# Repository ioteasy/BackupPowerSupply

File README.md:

# BackupPowerSupply
Module for backup power supply with 18650 - Li-ion battery

## Parameters
Input voltage: 5-24V

Output voltage Normal State: 4.4V

Output voltage Battery State: 4.3V

Max Current: 1A

## Used components
TPS54302 - Step-Down Converter (Input 4.5V-28V), Integrated MOSFETs for 3A continuous output current

LM2621 - Step-Up Converter (Input 1.2V-14V), Switch Current Limit 2.8A, Max switching frequenc 2MHz

MCP73831 - Single Cell Li-Ion Charge Management 

DW01 - Li-Ion Battery Protection

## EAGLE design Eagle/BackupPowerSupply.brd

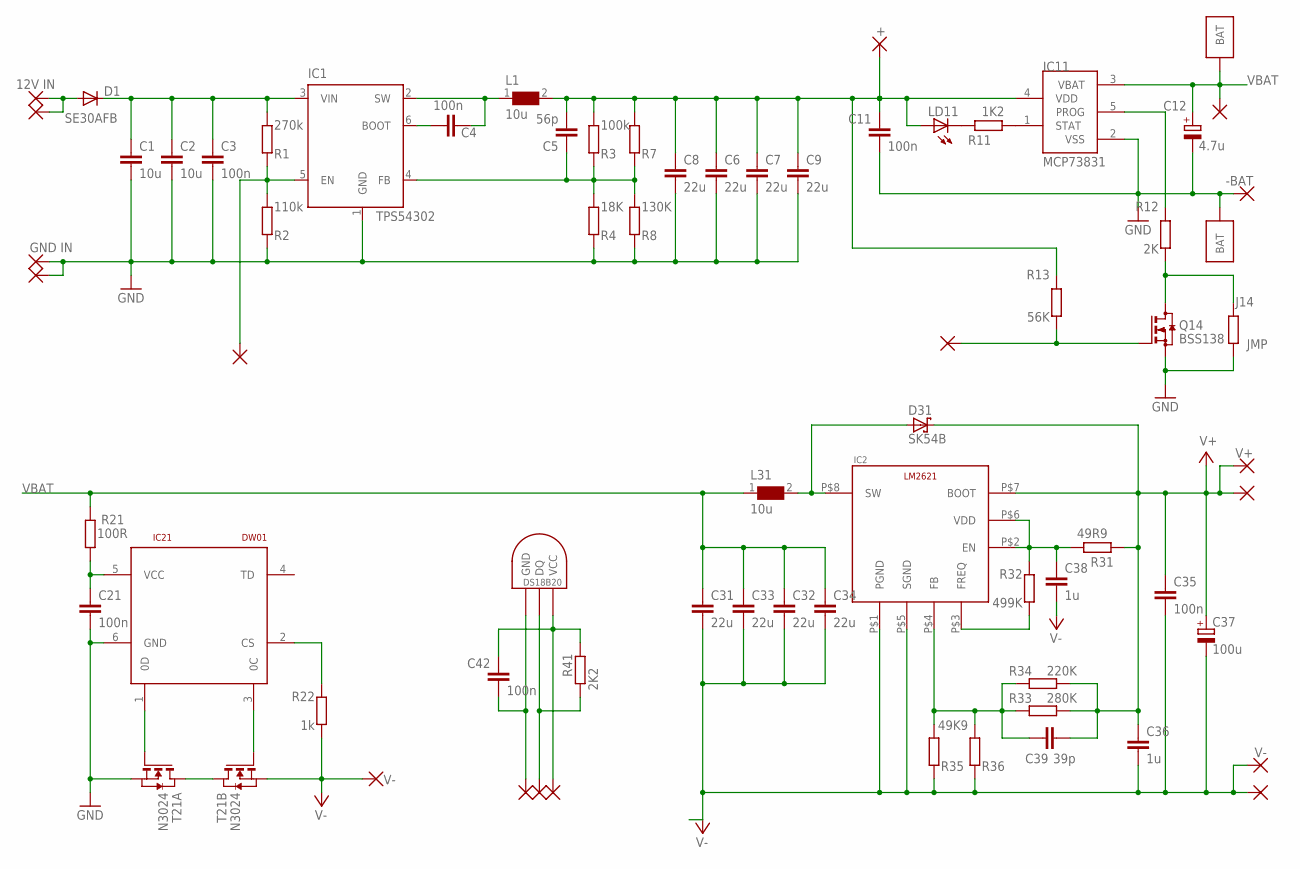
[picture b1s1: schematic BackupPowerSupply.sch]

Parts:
C1, C2: 10u; C1206
C3: 100n; C1206
C4, C11, C21, C35: 100n; C0805
C5: 56p; C0805
C6, C7, C8, C9, C31, C32, C33, C34: 22u; C0805
C12: 4.7u; SMC_A
C36, C38: 1u; C0805
C37: 100u; SMC_B
C39: 39p; C0805
C42: 100n; C0603
D1: SE30AFB; SOD-123_MINI-SMA
D31: SK54B; SMB
DS18B20: DS1820SOIC; DS18B20_SOIC
IC1: TPS54302; TSOT23-6_DDC
IC2: LM2621VSSOP8; VSSOP8
IC11: MCP73831; SOT23-5L
IC21: DW01; SOT23-6
J14: JMP; R0201
L1, L31: 10u; WE-LQS_8040
LD11: LEDCHIPLED_0805; CHIPLED_0805
PAD1: +BAT; PAD
PAD2: -BAT; PAD
PAD3: 12V IN; PAD
PAD4: GND IN; PAD
PAD5, PAD12: V+; PAD
PAD6, PAD9, PAD11, PAD19, PAD20, PAD21: V-; PAD
PAD7, PAD13: +; PAD
PAD8, PAD22: PAD
Q14: BSS138; SOT23
R1: 270k; M0805
R2: 110k; M0805
R3: 100k; M0805
R4: 18K; M0805
R7, R36: R-EU_M0805; M0805
R8: 130K; M0805
R11: 1K2; M0805
R12: 2K; M0805
R13: 56K; M0805
R21: 100R; M0805
R22: 1k; M0805
R31: 49R9; M0805
R32: 499K; M0805
R33: 280K; M0805
R34: 220K; M0805
R35: 49K9; M0805
R41: 2K2; R0603
T21: N3024; TSSOP-8
U$1, U$2: BAT_A
U$3: PAD

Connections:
C6: C5.2, IC1.4 (FB), R3.2, R4.1, R7.2, R8.1
FB2: C39.1, IC2.P$4 (FB), R33.1, R34.1, R35.1, R36.1
GND: C1.1, C2.1, C3.1, C6.1, C7.1, C8.1, C9.1, C11.1, C12.-, C21.1, IC1.1 (GND), IC11.2 (VSS), IC21.6 (GND), J14.1, PAD2.P$1, PAD4.P$1, PAD8.P$1, Q14.2 (S), R2.2, R4.2, R8.2, T21.2 (S), T21.3 (S), U$2.P$1, U$2.P$4
unnamed: C4.2, IC1.6 (BOOT)
unnamed: C42.1, DS18B20.GND, PAD21.P$1
unnamed: PAD7.P$1, Q14.1 (G), R13.1
unnamed: J14.2, Q14.3 (D), R12.1
unnamed: C5.1, C6.2, C7.2, C8.2, C9.2, C11.2, IC11.4 (VDD), L1.2, LD11.A, PAD13.P$1, R3.1, R7.1, R13.2
unnamed: IC11.1 (STAT), R11.1
unnamed: IC1.5 (EN), PAD22.P$1, R1.2, R2.1
unnamed: D1.A, PAD3.P$1, U$3.P$1
unnamed: IC11.5 (PROG), R12.2
unnamed: IC21.3 (0C), T21.5 (G)
unnamed: LD11.C, R11.2
unnamed: IC21.1 (0D), T21.4 (G)
unnamed: C38.2, IC2.P$2 (EN), IC2.P$6 (VDD), R31.2, R32.2
unnamed: IC2.P$3 (FREQ), R32.1
unnamed: T21.1 (D), T21.8 (D)
unnamed: IC21.2 (CS), R22.2
unnamed: DS18B20.DQ, PAD19.P$1, R41.2
unnamed: C21.2, IC21.5 (VCC), R21.1
unnamed: C42.2, DS18B20.VCC, PAD20.P$1, R41.1
OUT_DOWN: C4.1, IC1.2 (SW), L1.1
V+: C35.2, C36.2, C37.+, C39.2, D31.C, IC2.P$7 (BOOT), PAD5.P$1, PAD12.P$1, R31.1, R33.2, R34.2
V-: C31.1, C32.1, C33.1, C34.1, C35.1, C36.1, C37.-, C38.1, IC2.P$1 (PGND), IC2.P$5 (SGND), PAD6.P$1, PAD9.P$1, PAD11.P$1, R22.1, R35.2, R36.2, T21.6 (S), T21.7 (S)
VBAT: C12.+, C31.2, C32.2, C33.2, C34.2, IC11.3 (VBAT), L31.1, PAD1.P$1, R21.2, U$1.P$1, U$1.P$4
VIN_DOWN: C1.2, C2.2, C3.2, D1.C, IC1.3 (VIN), R1.1
VSW: D31.A, IC2.P$8 (SW), L31.2

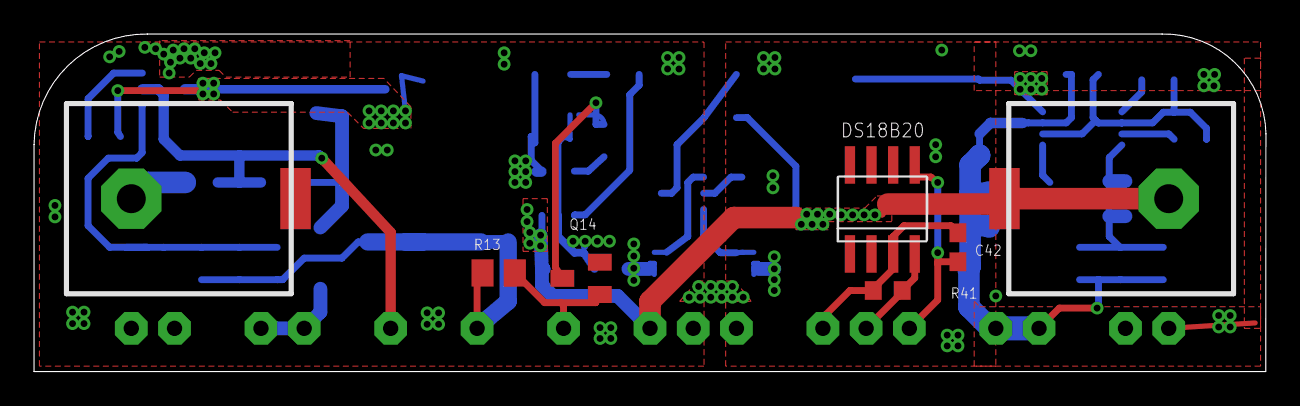
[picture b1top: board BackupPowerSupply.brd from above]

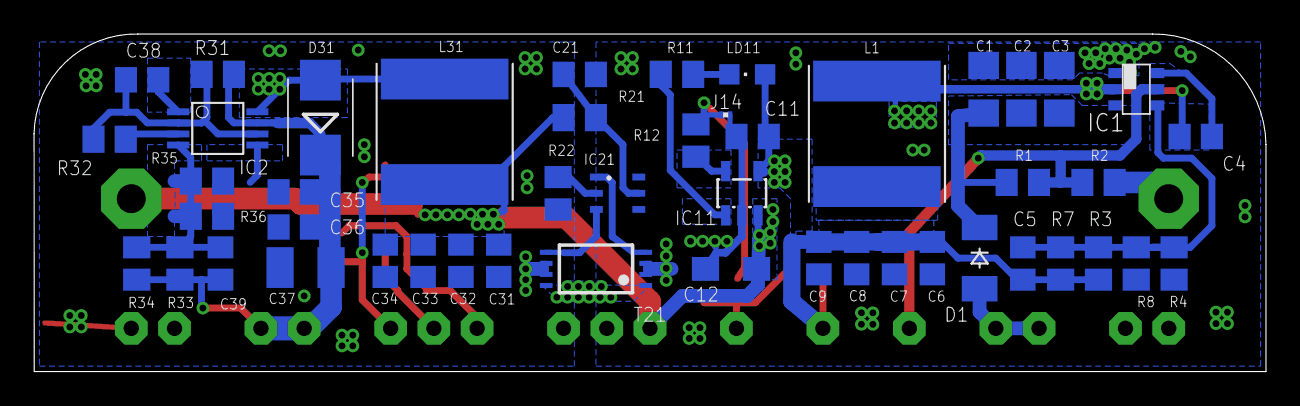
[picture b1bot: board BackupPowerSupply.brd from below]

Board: 2 copper layers, 72.4 x 19.8 mm, 72 parts (48 on the bottom side), 28 nets.

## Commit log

2018-05-21 add files
2018-05-22 add images
2018-05-22 readme

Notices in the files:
parts and their libraries:
Wurth_Elektronik_Passive_rev15b: Copyright: Würth Elektronik
